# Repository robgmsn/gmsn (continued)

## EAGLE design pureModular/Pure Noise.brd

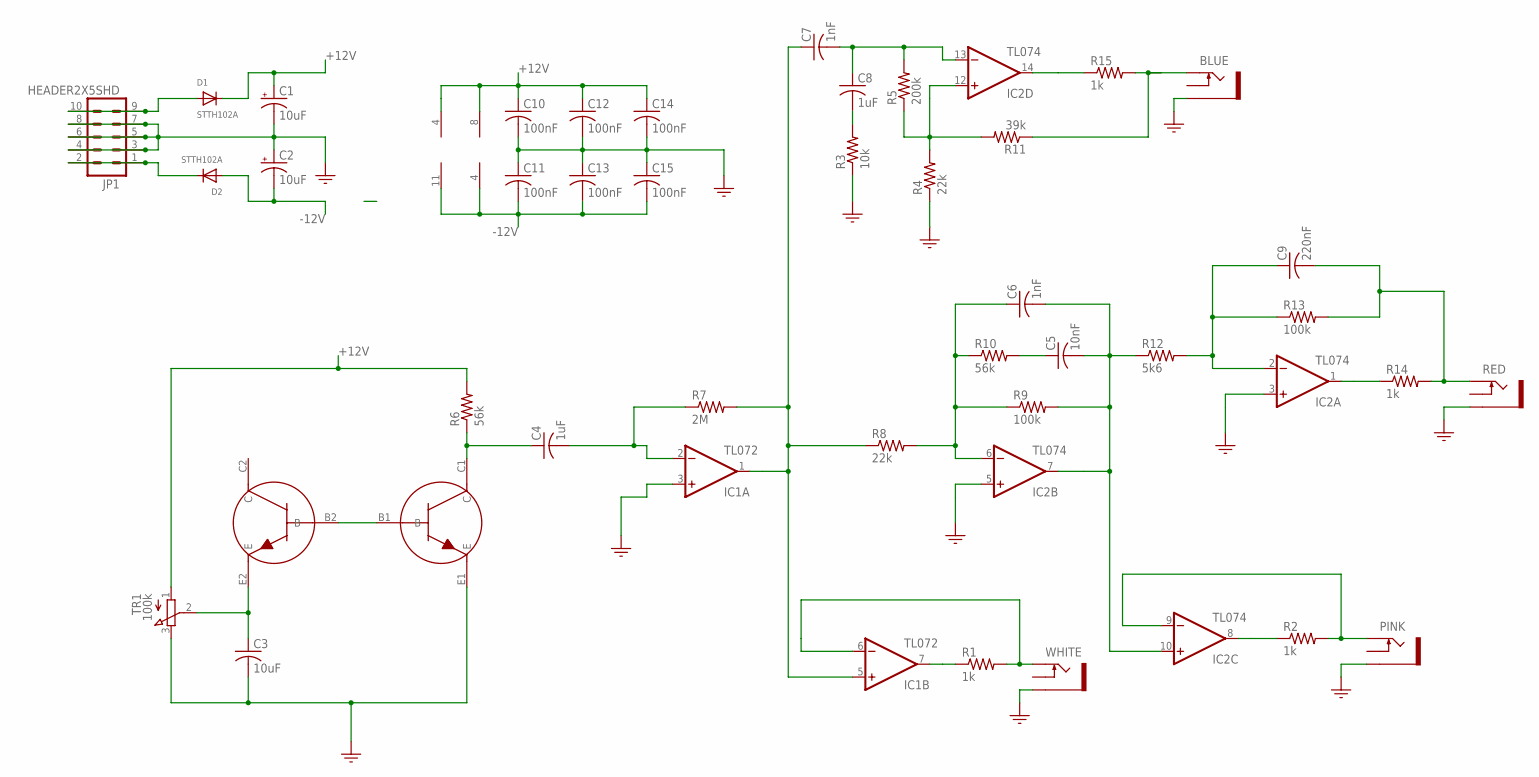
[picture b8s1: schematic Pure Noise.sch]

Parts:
BLUE: SOCKET_MONO_3.5MMPJ301M-12; PJ301M-12
C1, C2: 10uF; 153CLV-0505
C3: 10uF; C0805
C4, C8: 1uF; C0805
C5: 10nF; C0805
C6, C7: 1nF; C0805
C9: 220nF; C0805
C10, C11, C12, C13, C14, C15: 100nF; C0805
D1, D2: STTH102A; SMADIODE
IC1: TL072; SO08
IC2: TL074; SO14
JP1: HEADER2X5SHD; 2X5-SHROUDED
PINK: SOCKET_MONO_3.5MMPJ301M-12; PJ301M-12
R1, R2, R14, R15: 1k; R0805
R3: 10k; R0805
R4, R8: 22k; R0805
R5: 200k; R0805
R6, R10: 56k; R0805
R7: 2M; R0805
R9, R13: 100k; R0805
R11: 39k; R0805
R12: 5k6; R0805
RED: SOCKET_MONO_3.5MMPJ301M-12; PJ301M-12
T1: DMMT3904W-7-F; TRANS_PAIR
TR1: 100k; TRIMMER_TH
WHITE: SOCKET_MONO_3.5MMPJ301M-12; PJ301M-12

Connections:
+12V: C1.+, C10.1, C12.1, C14.1, D1.C, IC1.8 (V+), IC2.4 (V+), R6.2, TR1.1
-12V: C2.-, C11.2, C13.2, C15.2, D2.A, IC1.4 (V-), IC2.11 (V-)
BLUE: BLUE.TIP, R11.1, R15.2
GND: BLUE.GND (SLEEVE), C1.-, C2.+, C3.2, C10.2, C11.1, C12.2, C13.1, C14.2, C15.1, IC1.3 (+IN), IC2.3 (+IN), IC2.5 (+IN), JP1.3, JP1.4, JP1.5, JP1.6, JP1.7, JP1.8, PINK.GND (SLEEVE), R3.1, R4.1, RED.GND (SLEEVE), T1.E1 (E), TR1.3, WHITE.GND (SLEEVE)
unnamed: IC1.7 (OUT), R1.1
unnamed: IC2.8 (OUT), R2.1
unnamed: C8.2, R3.2
unnamed: C7.2, C8.1, IC2.13 (-IN), R5.2
unnamed: IC2.12 (+IN), R4.2, R5.1, R11.2
unnamed: C9.1, IC2.2 (-IN), R12.2, R13.1
unnamed: IC2.1 (OUT), R14.1
unnamed: D1.A, JP1.9, JP1.10
unnamed: D2.C, JP1.1, JP1.2
unnamed: IC2.14 (OUT), R15.1
unnamed: T1.B1 (B), T1.B2 (B)
unnamed: C3.1, T1.E2 (E), TR1.2
unnamed: C4.1, R6.1, T1.C1 (C)
unnamed: C4.2, IC1.2 (-IN), R7.1
unnamed: C6.1, IC2.6 (-IN), R8.2, R9.1, R10.1
unnamed: C5.1, R10.2
unnamed: C7.1, IC1.1 (OUT), IC1.5 (+IN), R7.2, R8.1
unnamed: C5.2, C6.2, IC2.7 (OUT), IC2.10 (+IN), R9.2, R12.1
PINK: IC2.9 (-IN), PINK.TIP, R2.2
RED: C9.2, R13.2, R14.2, RED.TIP
WHITE: IC1.6 (-IN), R1.2, WHITE.TIP

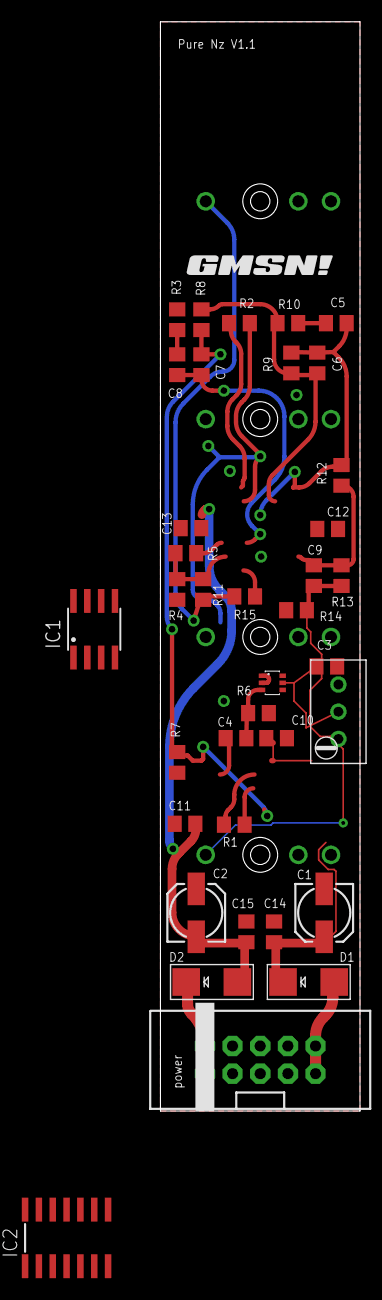
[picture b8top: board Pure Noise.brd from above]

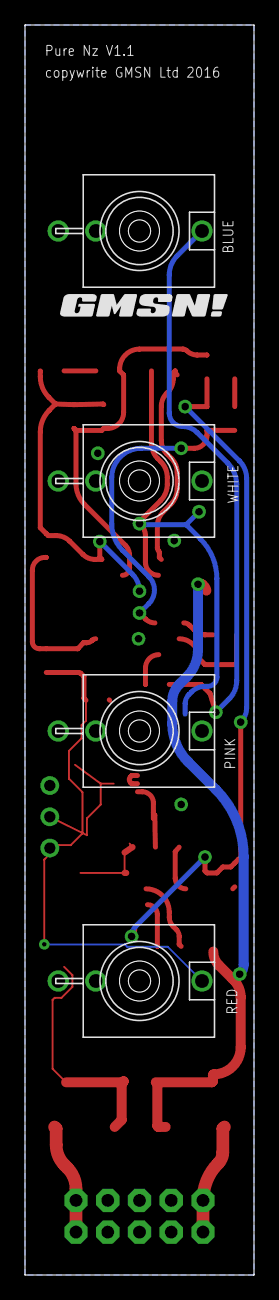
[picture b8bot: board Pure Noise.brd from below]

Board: 2 copper layers, 18.3 x 100.0 mm, 43 parts (5 on the bottom side), 25 nets.

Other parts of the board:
U$2, U$3: GMSN!_LOGO

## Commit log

2016-02-20 Initial Update to Readme
    Added THC and License meets.
2016-02-20 Adding THC Files
    THC Files
2021-04-01 Rename pureModular/Pure VCO v3 20171026.brd to pureModular/pureVCO/Pure VCO v3 20171026.brd
2021-04-01 Rename pureModular/Pure VCO v3 20171026.sch to pureModular/pureVCO/Pure VCO v3 20171026.sch
2021-04-01 Backlink to CADLAB.io has been added.
2021-04-01 Rename Pure VCO v3 20171026.brd to pureVCO.brd
2021-04-01 Rename Pure VCO v3 20171026.sch to pureVCO.sch
2021-04-01 Rename pureModular/GMSN DC Offset 20161229.brd to pureModular/pureDCOffset/DC Offset.brd
2021-04-01 Rename pureModular/GMSN DC Offset 20161229.sch to pureModular/pureDCOffset/DC Offset.sch
2021-04-01 Rename pureModular/GMSN Pure Power.brd to pureModular/purePower/GMSN Pure Power.brd
2021-04-01 Rename pureModular/GMSN Pure Power.sch to pureModular/purePower/GMSN Pure Power.sch
2021-04-01 Rename pureModular/GMSN Super Skiff Power v1 20170629.brd to pureModular/superSkiffPower/Super Skiff Power.brd
2021-04-01 Rename pureModular/GMSN Super Skiff Power v1 20170629.sch to pureModular/superSkiffPower/Super Skiff Power.sch
2021-04-01 Rename pureModular/Pure ADSR.brd to pureModular/pureADSR/Pure ADSR.brd
2021-04-01 Rename pureModular/Pure ADSR.sch to pureModular/pureADSR/Pure ADSR.sch
2021-04-01 Rename pureModular/Pure Digit Panel.brd to pureModular/pureDigit/Pure Digit Panel.brd
2021-04-01 Rename pureModular/Pure Digit.brd to pureModular/pureDigit/Pure Digit.brd
2021-04-01 Rename pureModular/Pure Digit.sch to pureModular/pureDigit/Pure Digit.sch
2021-04-01 Rename pureModular/Pure LFO PCB Panel.brd to pureModular/pureLFO/Pure LFO PCB Panel.brd
2021-04-01 Rename pureModular/Pure LFO.brd to pureModular/pureLFO/Pure LFO.brd
2021-04-01 Rename pureModular/Pure LFO.sch to pureModular/pureLFO/Pure LFO.sch
2021-04-01 Rename pureModular/Pure Noise PCB Panel.brd to pureModular/pureNoise/Pure Noise PCB Panel.brd
2021-04-01 Rename pureModular/Pure Noise.brd to pureModular/pureNoise/Pure Noise.brd
2021-04-01 Rename pureModular/Pure Noise.sch to pureModular/pureNoise/Pure Noise.sch
2021-04-01 Rename pureModular/Pure Power PCB Panel.brd to pureModular/powerPower/Pure Power PCB Panel.brd
2021-04-01 Rename pureModular/Pure Power Strip.brd to pureModular/purePowerStrip/Pure Power Strip.brd
2021-04-01 Rename pureModular/Pure Power Strip.sch to pureModular/purePowerStrip/Pure Power Strip.sch
2021-04-01 Rename pureModular/Pure Quantiser Panel v3 20171102.brd to pureModular/pureQuantiser/Pure Quantiser Panel.brd
2021-04-01 Rename pureModular/Pure Quantiser.brd to pureModular/pureQuantiser/Pure Quantiser.brd
2021-04-01 Rename pureModular/Pure Quantiser.sch to pureModular/pureQuantiser/Pure Quantiser.sch
2021-04-01 Rename pureModular/Pure SH PCB Panel.brd to pureModular/pureSH/Pure SH PCB Panel.brd
2021-04-01 Rename pureModular/Pure SH.brd to pureModular/pureSH/Pure SH.brd
2021-04-01 Rename pureModular/Pure SH.sch to pureModular/pureSH/Pure SH.sch
2021-04-01 Rename pureModular/Pure Sequencer.brd to pureModular/pureSequencer/Pure Sequencer.brd
2021-04-01 Rename pureModular/Pure Sequencer.sch to pureModular/pureSequencer/Pure Sequencer.sch
2021-04-01 Rename pureModular/Pure VCA PCB Panel.brd to pureModular/pureVCA/Pure VCA PCB Panel.brd
2021-04-01 Rename pureModular/Pure VCA.brd to pureModular/pureVCA/Pure VCA.brd
2021-04-01 Rename pureModular/Pure VCA.sch to pureModular/pureVCA/Pure VCA.sch
2021-04-01 Rename pureModular/Pure VCF.brd to pureModular/pureVCF/Pure VCF.brd
2021-04-01 Rename pureModular/Pure VCF.sch to pureModular/pureVCF/Pure VCF.sch
2021-04-01 Rename pureModular/Safety Valve.sch to LMNC/Safety Valve.sch
2021-04-01 Files moved to correct directories
2021-04-01 more tidying
2021-04-06 Wrong design uploaded.
2021-04-06 Wrong design uploaded
2021-04-10 VCO Updated to V3
2021-04-12 Minor corrections. Awaiting Testing. No ready for public consumption.
2021-04-14 VCO 3.1
    Changed mixer from Average to Sum. Mixer outputs are now inversions of the individual out. Might be useful?
    Resistor values around mixer reduced to 10k, inline with low noise techniques.
2021-04-14 VCF 2.5
    VCF Updated to V2.5 14/04/21
    Library updated to 3D models.
    Changed the CV mixer from Average to Sum and added inverter stage to retain consistency.
    Some resistor values reduced to 10K, inline with low noise techniques.
    Rerouted and reduced some traces.
2021-04-14 VCA 2.3
    VCA Updated to V2.3 14/4/21
    Library updated to include 3D models.
    Traces rerouted.
    Weird shorted cap removed. WTF?
2021-04-14 Sample and Hold 1.5
    S&H Updated to V1.5 14/4/21
    Library updated to include 3D models.
    Traces rerouted.
2021-04-14 Sample and Hold 1.51
    Updated Readme with 1.5 changes
2021-04-14 ADSR 2.2
    ADSR Updated to V2.2 14/4/21
    Library updated to include 3D models.
    Traces rerouted.
    DAC output filter remodelled.
    Power replaced so 5V comes from power supply rather than 12V, in line with low noise techniques.
2021-04-16 Pure ADSR Moved to it's own repo
    https://github.com/robgmsn/PureADSR
2021-04-16 Pure LFO moved to it's own repo
    https://github.com/robgmsn/PureLFO
2021-04-16 Pure Noise moved to it's own repo
    https://github.com/robgmsn/PureNoise
2021-04-16 Pure Sample and Hold moved to it's own repo
    https://github.com/robgmsn/PureSandH
2021-04-16 Pure Sequencer moved to it's own repo
    https://github.com/robgmsn/PureSequencer
2021-04-16 Pure VCA moved to it's own repo
    https://github.com/robgmsn/PureVCA
2021-04-16 Pure VCF moved to it's own repo
    https://github.com/robgmsn/PureVCF
2021-04-16 Pure VCO moved to it's own repo
    https://github.com/robgmsn/PureVCO
2021-04-25 Pure Digit moved to the main Digit Repo
    https://github.com/robgmsn/PureDigit
2021-04-25 Skiff Power moved to its own repo
    https://github.com/robgmsn/SkiffPower
2021-04-25 Power Strip moved to it's own repo
    https://github.com/robgmsn/PowerStrip
2021-04-25 DC Offset moved to it's own repo
    https://github.com/robgmsn/DCOffset
